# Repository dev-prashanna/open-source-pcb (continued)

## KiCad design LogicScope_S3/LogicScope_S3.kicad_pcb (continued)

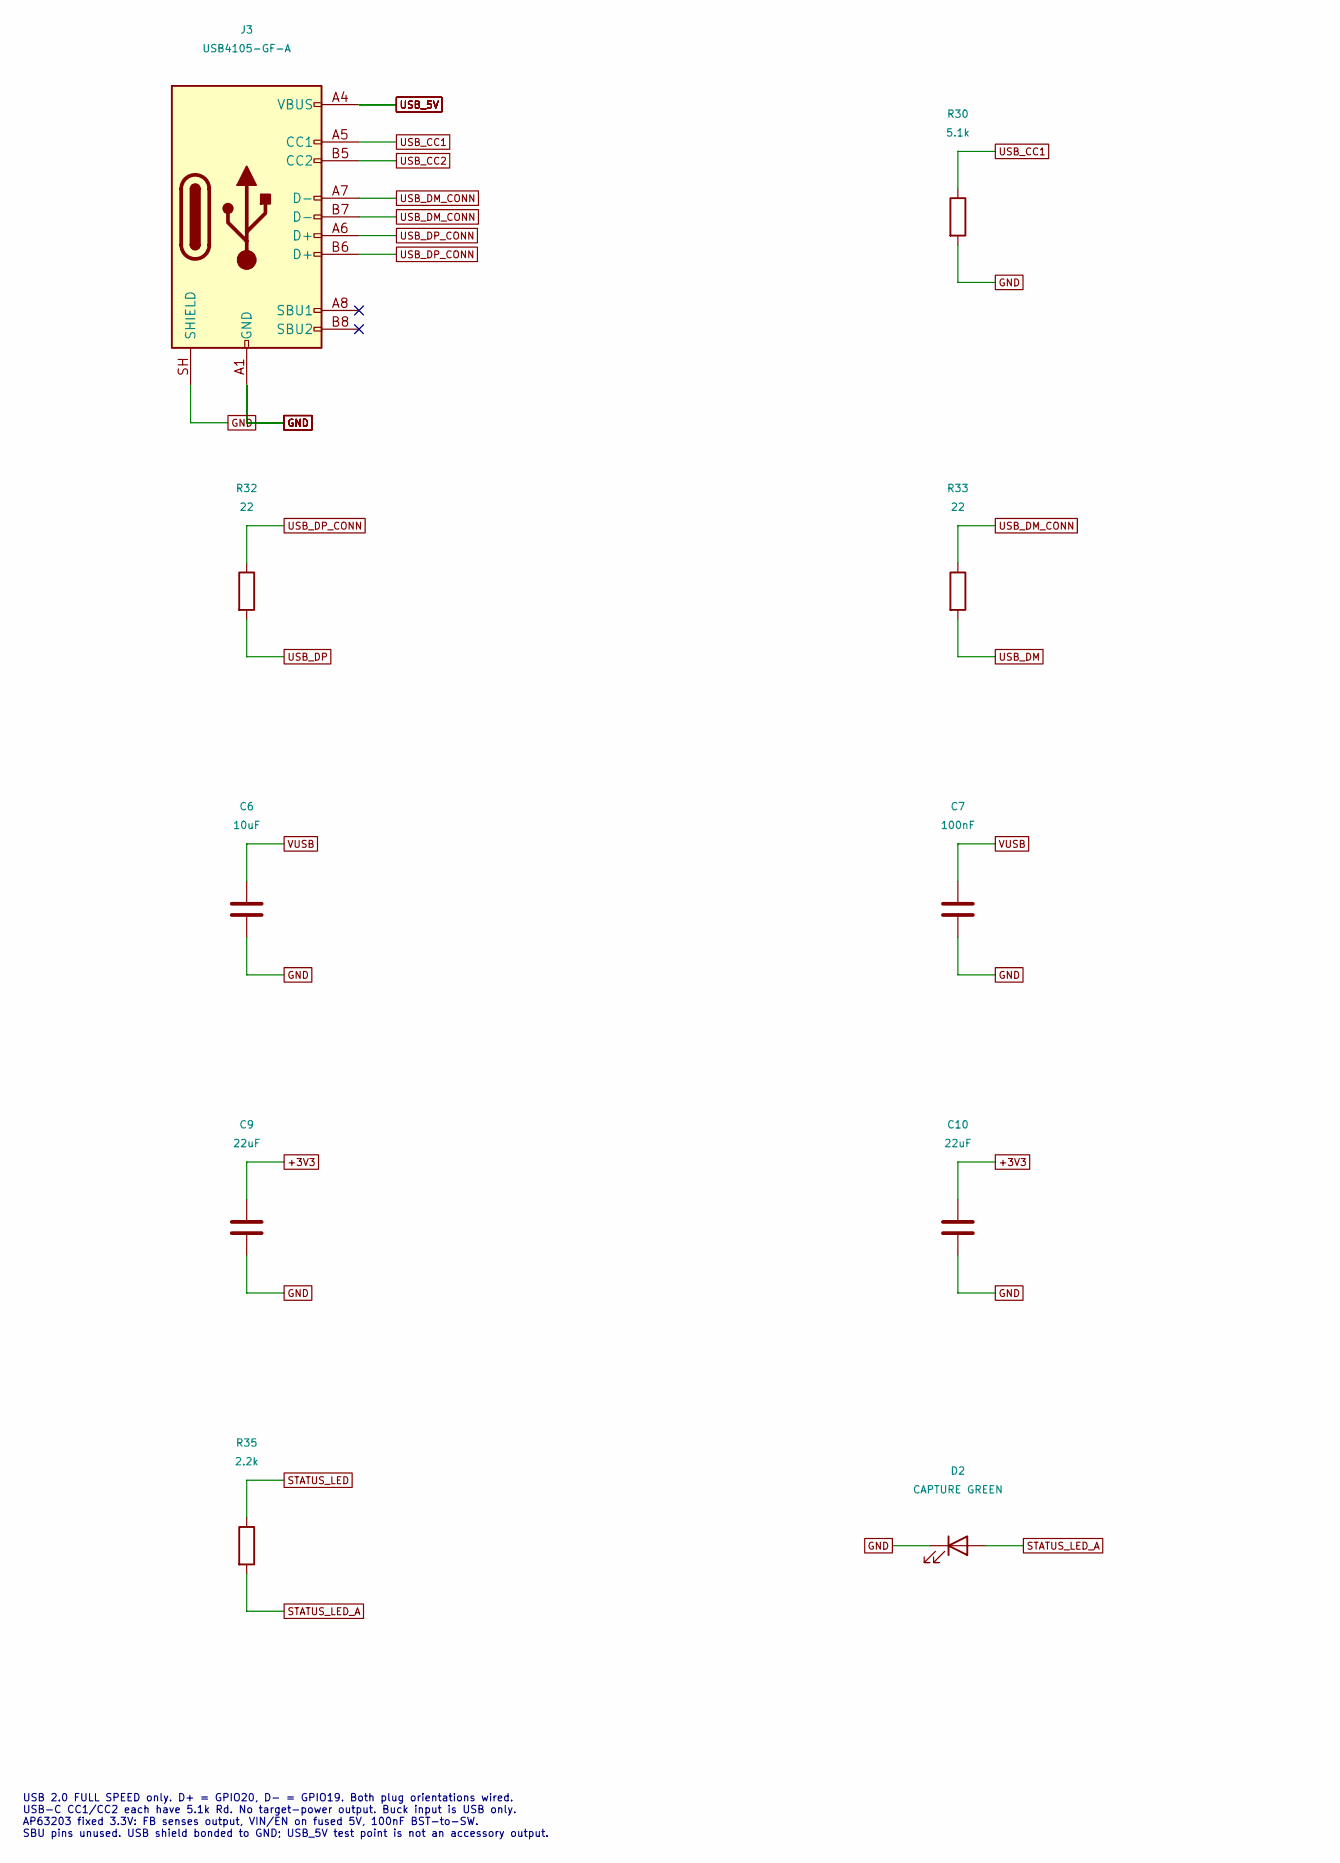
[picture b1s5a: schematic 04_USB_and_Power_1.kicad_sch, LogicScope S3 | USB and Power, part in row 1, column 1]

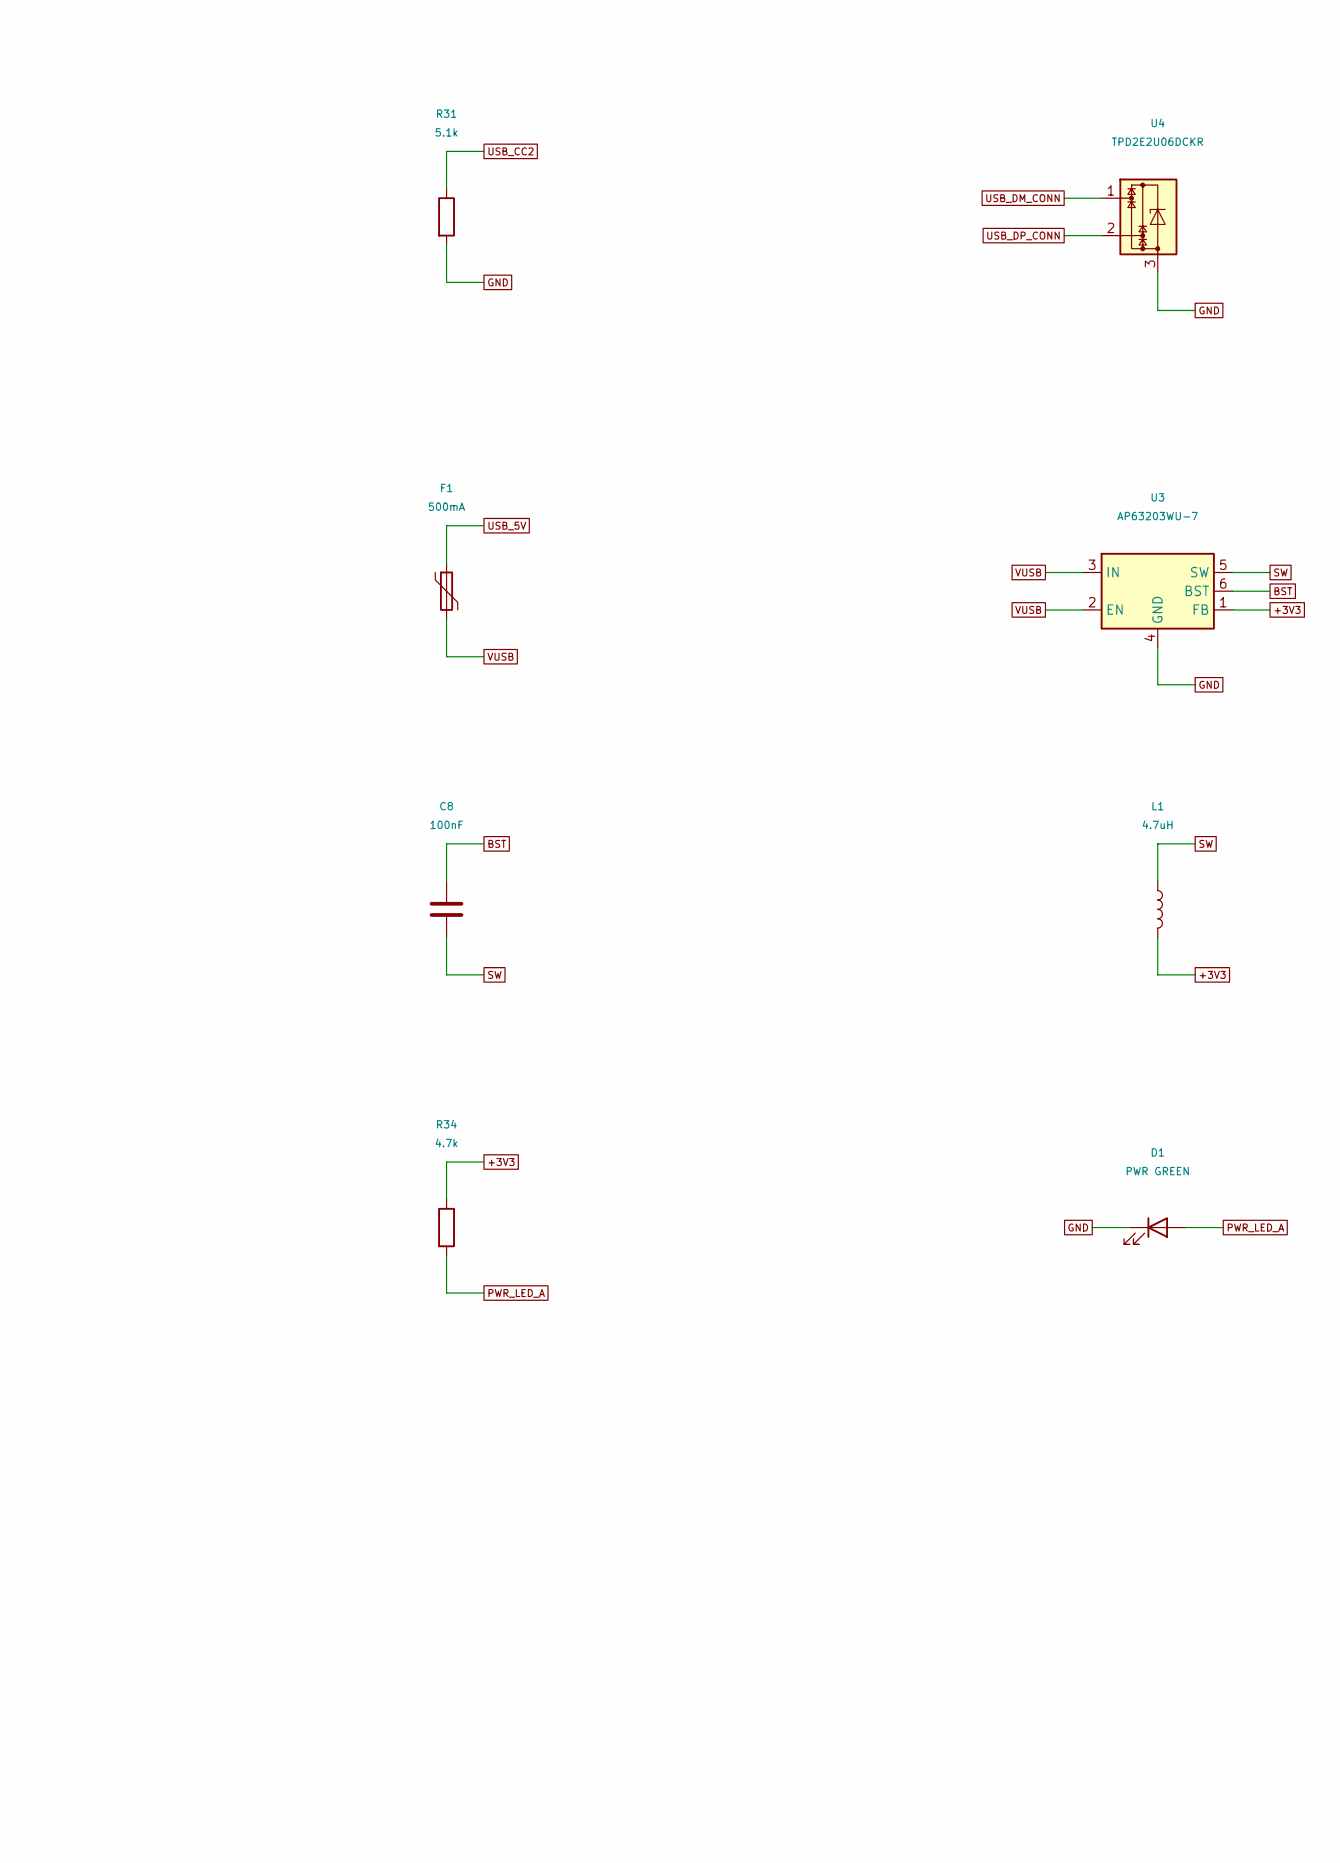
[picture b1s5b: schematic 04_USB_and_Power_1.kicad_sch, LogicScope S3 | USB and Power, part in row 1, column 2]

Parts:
C6: 10uF; C_0805_2012Metric; MPN GRM21BR61A106KE19L
C7, C8: 100nF; C_0603_1608Metric; MPN GRM188R71C104KA01D
C9, C10: 22uF; C_0805_2012Metric; MPN GRM21BR60J226ME39L
D1: PWR GREEN; LED_0603_1608Metric; MPN LTST-C190KGKT
D2: CAPTURE GREEN; LED_0603_1608Metric; MPN LTST-C190KGKT
F1: 500mA; Fuse_1206_3216Metric; MPN 1206L050YR
J3: USB4105-GF-A; USB_C_Receptacle_GCT_USB4105-xx-A_16P_TopMnt_Horizontal; MPN USB4105-GF-A
L1: 4.7uH; L_Bourns-SRN4018; MPN SRN4018-4R7M
R30, R31: 5.1k; R_0603_1608Metric; MPN RC0603FR-075K1L
R32, R33: 22; R_0402_1005Metric; MPN RC0402FR-0722RL
R34: 4.7k; R_0603_1608Metric; MPN RC0603FR-074K7L
R35: 2.2k; R_0603_1608Metric; MPN RC0603FR-072K2L
U3: AP63203WU-7; TSOT-23-6; MPN AP63203WU-7
U4: TPD2E2U06DCKR; SOT-323_SC-70; MPN TPD2E2U06DCKR

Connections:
+3V3: C9.1, C10.1, L1.2, R34.1, U3.1 (FB); also elsewhere on the board
BST: C8.1, U3.6 (BST)
GND: C6.2, C7.2, C9.2, C10.2, D1.1 (K), D2.1 (K), J3.A1 (GND), J3.A12 (GND), J3.B1 (GND), J3.B12 (GND), J3.SH (SHIELD), R30.2, R31.2, U3.4 (GND), U4.3; also elsewhere on the board
PWR_LED_A: D1.2 (A), R34.2
STATUS_LED: R35.1; also elsewhere on the board
STATUS_LED_A: D2.2 (A), R35.2
SW: C8.2, L1.1, U3.5 (SW)
USB_5V: F1.1, J3.A4 (VBUS), J3.A9 (VBUS), J3.B4 (VBUS), J3.B9 (VBUS); also elsewhere on the board
USB_CC1: J3.A5 (CC1), R30.1
USB_CC2: J3.B5 (CC2), R31.1
USB_DM: R33.2; also elsewhere on the board
USB_DM_CONN: J3.A7 (D-), J3.B7 (D-), R33.1, U4.1
USB_DP: R32.2; also elsewhere on the board
USB_DP_CONN: J3.A6 (D+), J3.B6 (D+), R32.1, U4.2
VUSB: C6.1, C7.1, F1.2, U3.2 (EN), U3.3 (IN); also elsewhere on the board

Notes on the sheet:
USB 2.0 FULL SPEED only. D+ = GPIO20, D- = GPIO19. Both plug orientations wired. USB-C CC1/CC2 each have 5.1k Rd. No target-power output. Buck input is USB only. AP63203 fixed 3.3V: FB senses output, VIN/EN on fused 5V, 100nF BST-to-SW. SBU pins unused. USB shield bonded to GND; USB_5V test point i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

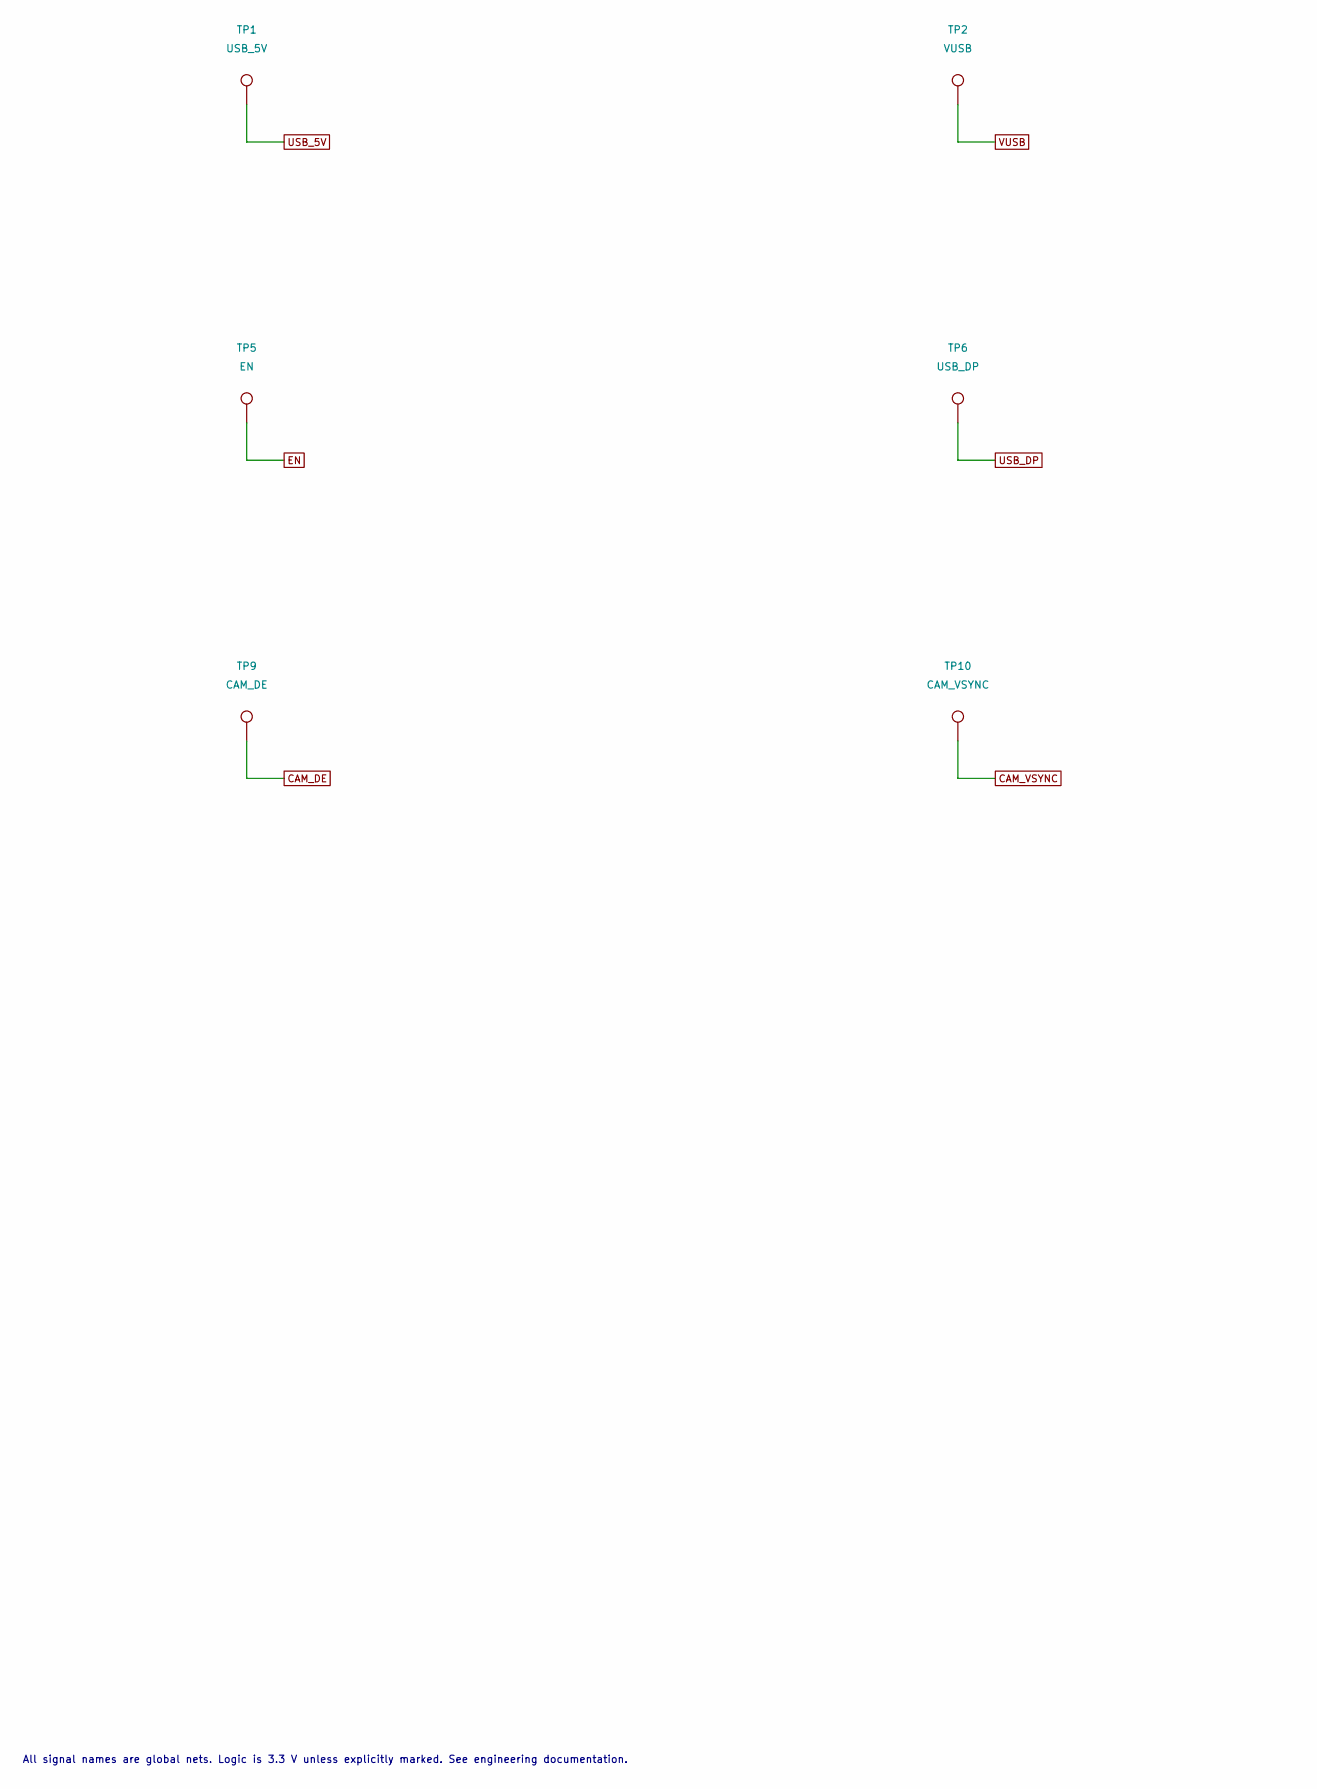
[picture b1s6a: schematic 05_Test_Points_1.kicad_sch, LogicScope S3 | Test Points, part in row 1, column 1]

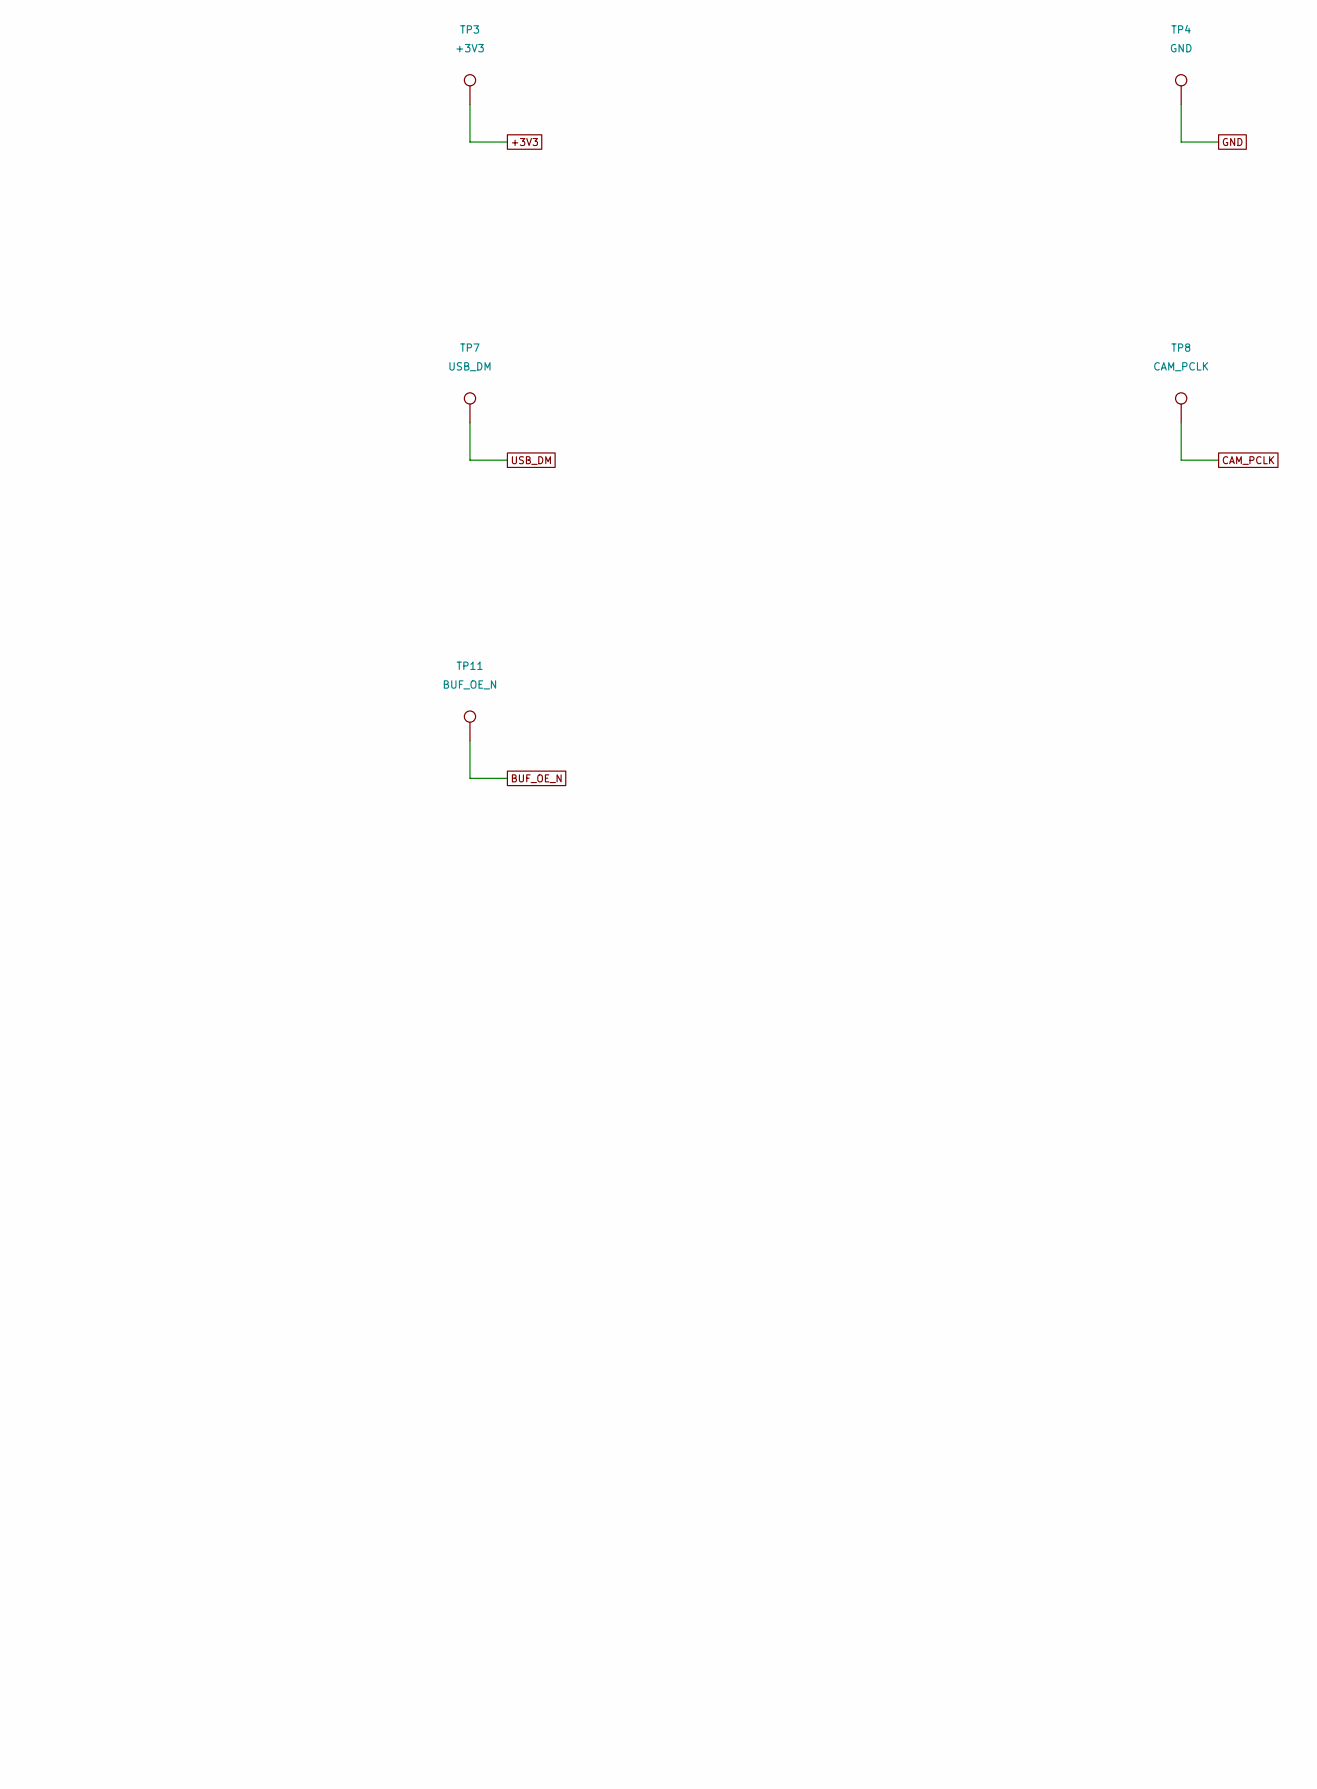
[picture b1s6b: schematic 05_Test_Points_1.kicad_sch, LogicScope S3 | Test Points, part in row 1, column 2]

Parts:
TP1: USB_5V; TestPoint_Pad_D1.0mm; MPN PCB_PAD
TP2: VUSB; TestPoint_Pad_D1.0mm; MPN PCB_PAD
TP3: +3V3; TestPoint_Pad_D1.0mm; MPN PCB_PAD
TP4: GND; TestPoint_Pad_D1.0mm; MPN PCB_PAD
TP5: EN; TestPoint_Pad_D1.0mm; MPN PCB_PAD
TP6: USB_DP; TestPoint_D0.5mm; MPN PCB_PAD
TP7: USB_DM; TestPoint_D0.5mm; MPN PCB_PAD
TP8: CAM_PCLK; TestPoint_Pad_D1.0mm; MPN PCB_PAD
TP9: CAM_DE; TestPoint_Pad_D1.0mm; MPN PCB_PAD
TP10: CAM_VSYNC; TestPoint_Pad_D1.0mm; MPN PCB_PAD
TP11: BUF_OE_N; TestPoint_Pad_D1.0mm; MPN PCB_PAD

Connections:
+3V3: TP3.1; also elsewhere on the board
BUF_OE_N: TP11.1; also elsewhere on the board
CAM_DE: TP9.1; also elsewhere on the board
CAM_PCLK: TP8.1; also elsewhere on the board
CAM_VSYNC: TP10.1; also elsewhere on the board
EN: TP5.1; also elsewhere on the board
GND: TP4.1; also elsewhere on the board
USB_5V: TP1.1; also elsewhere on the board
USB_DM: TP7.1; also elsewhere on the board
USB_DP: TP6.1; also elsewhere on the board
VUSB: TP2.1; also elsewhere on the board

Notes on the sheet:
All signal names are global nets. Logic is 3.3 V unless explicitly marked. See engineering documentation.

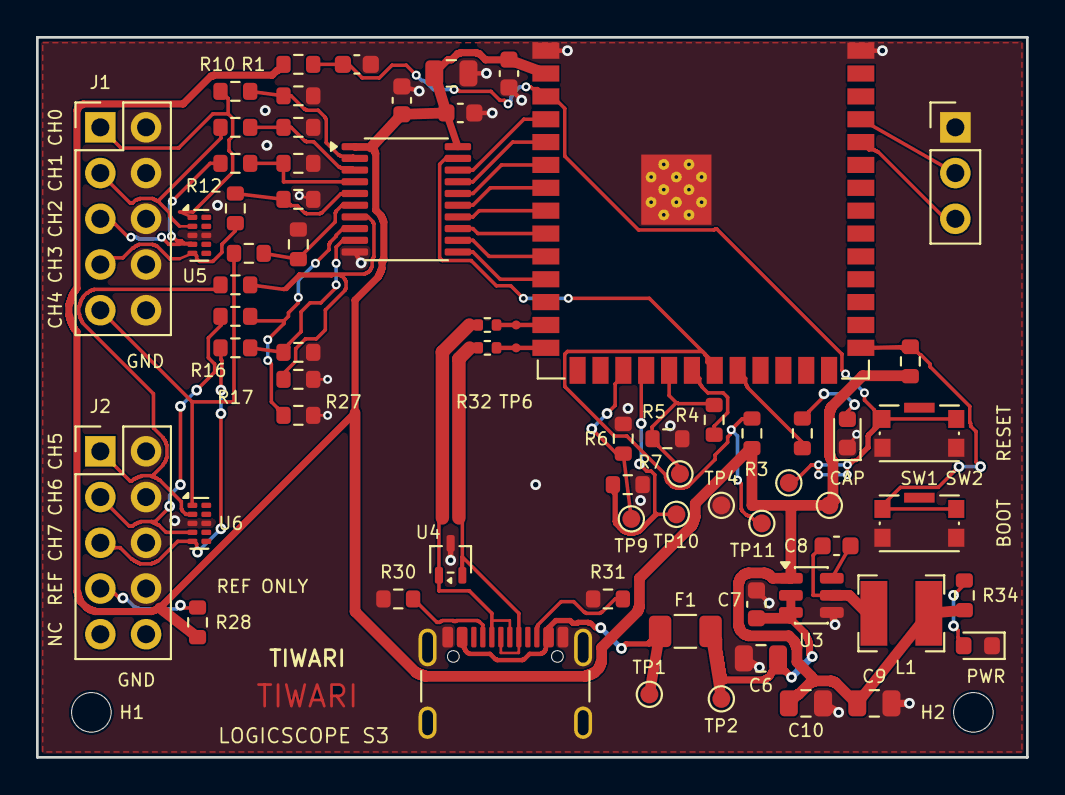
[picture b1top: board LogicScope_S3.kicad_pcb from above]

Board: 2 copper layers, 55.0 x 40.0 mm, 69 parts (0 on the bottom side), 49 nets.

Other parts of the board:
H1, H2: MountingHole_2.2mm_M2

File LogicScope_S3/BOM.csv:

Reference,Value,MPN,Manufacturer,Footprint,DNP,Datasheet
U1,ESP32-S3-WROOM-1-N8R2,ESP32-S3-WROOM-1-N8R2,Espressif,LogicScope:ESP32-S3-WROOM-1_Overhang,NO,https://documentation.espressif.com/esp32-s3-wroom-1_wroom-1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
C1,100nF,GRM188R71C104KA01D,Murata,Capacitor_SMD:C_0603_1608Metric,NO,https://www.murata.com/en-global/products/capacitor/ceramicc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
C2,10uF,GRM21BR61A106KE19L,Murata,Capacitor_SMD:C_0805_2012Metric,NO,https://www.murata.com/en-global/products/capacitor/ceramicc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
R1,10k,RC0603FR-0710KL,Yageo,Resistor_SMD:R_0603_1608Metric,NO,https://www.yageo.com/en/Product/Index/rchip
C3,1uF,GRM188R61A105KA61D,Murata,Capacitor_SMD:C_0603_1608Metric,NO,https://www.murata.com/en-global/products/capacitor/ceramicc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
R2,10k,RC0603FR-0710KL,Yageo,Resistor_SMD:R_0603_1608Metric,NO,https://www.yageo.com/en/Product/Index/rchip
R3,10k,RC0603FR-0710KL,Yageo,Resistor_SMD:R_0603_1608Metric,NO,https://www.yageo.com/en/Product/Index/rchip
R4,33,RC0603FR-0733RL,Yageo,Resistor_SMD:R_0603_1608Metric,NO,https://www.yageo.com/en/Product/Index/rchip
R5,100k,RC0603FR-07100KL,Yageo,Resistor_SMD:R_0603_1608Metric,NO,https://www.yageo.com/en/Product/Index/rchip
R6,100k,RC0603FR-07100KL,Yageo,Resistor_SMD:R_0603_1608Metric,NO,https://www.yageo.com/en/Product/Index/rchip
R7,100k,RC0603FR-07100KL,Yageo,Resistor_SMD:R_0603_1608Metric,NO,https://www.yageo.com/en/Product/Index/rchip
SW1,RESET,KMR221GLFS,C&K,Button_Switch_SMD:SW_Push_1P1T-SH_NO_CK_KMR2xxG,NO,https://www.ckswitches.com/media/1464/kmr2.pdf
SW2,BOOT,KMR221GLFS,C&K,Button_Switch_SMD:SW_Push_1P1T-SH_NO_CK_KMR2xxG,NO,https://www.ckswitches.com/media/1464/kmr2.pdf
J4,DEBUG 3V3 UART,61300311121,Wurth Elektronik,Connector_PinHeader_2.54mm:PinHeader_1x03_P2.54mm_Vertical,NO,https://www.we-online.com/en/components/products/WR-PHD_254M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
J1,CH0..4 + GROUNDS,61301021121,Wurth Elektronik,Connector_PinHeader_2.54mm:PinHeader_2x05_P2.54mm_Vertical,NO,https://www.we-online.com/en/components/products/WR-PHD_254M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
J2,CH5..7 / REF ONLY,61301021121,Wurth Elektronik,Connector_PinHeader_2.54mm:PinHeader_2x05_P2.54mm_Vertical,NO,https://www.we-online.com/en/components/products/WR-PHD_254M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
R10,220,RC0603FR-07220RL,Yageo,Resistor_SMD:R_0603_1608Metric,NO,https://www.yageo.com/en/Product/Index/rchip
R20,100k,RC0603FR-07100KL,Yageo,Resistor_SMD:R_0603_1608Metric,NO,https://www.yageo.com/en/Product/Index/rchip
R11,220,RC0603FR-07220RL,Yageo,Resistor_SMD:R_0603_1608Metric,NO,https://www.yageo.com/en/Product/Index/rchip
R21,100k,RC0603FR-07100KL,Yageo,Resistor_SMD:R_0603_1608Metric,NO,https://www.yageo.com/en/Product/Index/rchip
R12,220,RC0603FR-07220RL,Yageo,Resistor_SMD:R_0603_1608Metric,NO,https://www.yageo.com/en/Product/Index/rchip
R22,100k,RC0603FR-07100KL,Yageo,Resistor_SMD:R_0603_1608Metric,NO,https://www.yageo.com/en/Product/Index/rchip
R13,220,RC0603FR-07220RL,Yageo,Resistor_SMD:R_0603_1608Metric,NO,https://www.yageo.com/en/Product/Index/rchip
R23,100k,RC0603FR-07100KL,Yageo,Resistor_SMD:R_0603_1608Metric,NO,https://www.yageo.com/en/Product/Index/rchip
R14,220,RC0603FR-07220RL,Yageo,Resistor_SMD:R_0603_1608Metric,NO,https://www.yageo.com/en/Product/Index/rchip
R24,100k,RC0603FR-07100KL,Yageo,Resistor_SMD:R_0603_1608Metric,NO,https://www.yageo.com/en/Product/Index/rchip
R15,220,RC0603FR-07220RL,Yageo,Resistor_SMD:R_0603_1608Metric,NO,https://www.yageo.com/en/Product/Index/rchip
R25,100k,RC0603FR-07100KL,Yageo,Resistor_SMD:R_0603_1608Metric,NO,https://www.yageo.com/en/Product/Index/rchip
R16,220,RC0603FR-07220RL,Yageo,Resistor_SMD:R_0603_1608Metric,NO,https://www.yageo.com/en/Product/Index/rchip
R26,100k,RC0603FR-07100KL,Yageo,Resistor_SMD:R_0603_1608Metric,NO,https://www.yageo.com/en/Product/Index/rchip
R17,220,RC0603FR-07220RL,Yageo,Resistor_SMD:R_0603_1608Metric,NO,https://www.yageo.com/en/Product/Index/rchip
R27,100k,RC0603FR-07100KL,Yageo,Resistor_SMD:R_0603_1608Metric,NO,https://www.yageo.com/en/Product/Index/rchip
R28,10k,RC0603FR-0710KL,Yageo,Resistor_SMD:R_0603_1608Metric,NO,https://www.yageo.com/en/Product/Index/rchip
U5,TPD4E05U06DQAR (OPTIONAL),TPD4E05U06DQAR,Texas Instruments,Package_SON:USON-10_2.5x1.0mm_P0.5mm,YES,https://www.ti.com/lit/ds/symlink/tpd4e05u06.pdf
U6,TPD4E05U06DQAR (OPTIONAL),TPD4E05U06DQAR,Texas Instruments,Package_SON:USON-10_2.5x1.0mm_P0.5mm,YES,https://www.ti.com/lit/ds/symlink/tpd4e05u06.pdf
U2,SN74LVC245APW,SN74LVC245APW,Texas Instruments,Package_SO:TSSOP-20_4.4x6.5mm_P0.65mm,NO,https://www.ti.com/lit/ds/symlink/sn74lvc245a.pdf
C4,100nF,GRM188R71C104KA01D,Murata,Capacitor_SMD:C_0603_1608Metric,NO,https://www.murata.com/en-global/products/capacitor/ceramicc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
C5,1uF,GRM188R61A105KA61D,Murata,Capacitor_SMD:C_0603_1608Metric,NO,https://www.murata.com/en-global/products/capacitor/ceramicc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
J3,USB4105-GF-A,USB4105-GF-A,GCT,Connector_USB:USB_C_Receptacle_GCT_USB4105-xx-A_16P_TopMnt_Horizontal,NO,https://gct.co/connector/usb4105
R30,5.1k,RC0603FR-075K1L,Yageo,Resistor_SMD:R_0603_1608Metric,NO,https://www.yageo.com/en/Product/Index/rchip
R31,5.1k,RC0603FR-075K1L,Yageo,Resistor_SMD:R_0603_1608Metric,NO,https://www.yageo.com/en/Product/Index/rchip
U4,TPD2E2U06DCKR,TPD2E2U06DCKR,Texas Instruments,Package_TO_SOT_SMD:SOT-323_SC-70,NO,https://www.ti.com/lit/ds/symlink/tpd2e2u06.pdf
R32,22,RC0402FR-0722RL,Yageo,Resistor_SMD:R_0402_1005Metric,NO,https://www.yageo.com/en/Product/Index/rchip
R33,22,RC0402FR-0722RL,Yageo,Resistor_SMD:R_0402_1005Metric,NO,https://www.yageo.com/en/Product/Index/rchip
F1,500mA,1206L050YR,Littelfuse,Fuse:Fuse_1206_3216Metric,NO,https://www.littelfuse.com/products/polyswitch-resettable-pp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
U3,AP63203WU-7,AP63203WU-7,Diodes Incorporated,Package_TO_SOT_SMD:TSOT-23-6,NO,https://www.diodes.com/assets/Datasheets/AP63200-AP63201-AP6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
C6,10uF,GRM21BR61A106KE19L,Murata,Capacitor_SMD:C_0805_2012Metric,NO,https://www.murata.com/en-global/products/capacitor/ceramicc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
C7,100nF,GRM188R71C104KA01D,Murata,Capacitor_SMD:C_0603_1608Metric,NO,https://www.murata.com/en-global/products/capacitor/ceramicc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
C8,100nF,GRM188R71C104KA01D,Murata,Capacitor_SMD:C_0603_1608Metric,NO,https://www.murata.com/en-global/products/capacitor/ceramicc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
L1,4.7uH,SRN4018-4R7M,Bourns,Inductor_SMD:L_Bourns-SRN4018,NO,https://www.bourns.com/docs/product-datasheets/srn4018.pdf
C9,22uF,GRM21BR60J226ME39L,Murata,Capacitor_SMD:C_0805_2012Metric,NO,https://www.murata.com/en-global/products/capacitor/ceramicc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
C10,22uF,GRM21BR60J226ME39L,Murata,Capacitor_SMD:C_0805_2012Metric,NO,https://www.murata.com/en-global/products/capacitor/ceramicc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
R34,4.7k,RC0603FR-074K7L,Yageo,Resistor_SMD:R_0603_1608Metric,NO,https://www.yageo.com/en/Product/Index/rchip
D1,PWR GREEN,LTST-C190KGKT,Lite-On,LED_SMD:LED_0603_1608Metric,NO,
R35,2.2k,RC0603FR-072K2L,Yageo,Resistor_SMD:R_0603_1608Metric,NO,https://www.yageo.com/en/Product/Index/rchip
D2,CAPTURE GREEN,LTST-C190KGKT,Lite-On,LED_SMD:LED_0603_1608Metric,NO,

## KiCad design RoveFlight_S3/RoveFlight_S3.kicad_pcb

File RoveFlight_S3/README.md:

# RoveFlight S3

**RF-S3-A0 — compact ESP32-S3 flight-controller engineering prototype for a 1S brushed quadcopter.**

Hardware layout release completed 2026-11-09: **ERC 0, DRC 0, unconnected items 0, schematic/PCB parity issues 0**, with all 15 independent connectivity checks passing. [Manufacturing package](fabrication/) and [validation evidence](docs/Manufacturing_Readiness.md) are included. Via-in-pad filling/capping and fabricator DFM are required; physical qualification remains open.

A real native KiCad design with ESP32-S3-WROOM-1-N8R2, four independent brushed-motor MOSFET stages, a hardware arming latch and watchdog, BMI270 SPI IMU, BMP390 SPI barometer, battery voltage/current monitoring, downward VL53L1X, IR receiver, USB-C and receiver/optical-flow/debug expansion.

Open **RoveFlight_S3.kicad_pro** in KiCad 10. The root schematic links the functional sheets. The PCB is 45 x 45 mm, six layers, nominal 1.0-mm thickness, two-sided assembly, with 25.5-mm-square M2 mounting and an antenna overhang. The assembled antenna extends 6.75 mm beyond the forward edge. No flight-ready, fabricated-board, RF, thermal or EMC qualification is claimed.

## Electrical limits

- Protected 1S LiPo, 3.1–4.2 V. No onboard charger or cell-protection IC.
- Brushed motors only. Proposed envelope: 1 A continuous per motor, 4 A aggregate, 2 A single-channel stall for at most 100 ms, subject to actual motor/propeller and thermal qualification.
- All external signals are 3.3 V. Receiver supply/interface compatibility must be checked; no 5-V UART tolerance or SBUS inverter is provided.
- Remove JP1 to disconnect motor enable physically. USB insertion clears the arming latch. Every detected fault requires a fresh arming command; see the exact reset caveat in the safety document.
- Local attitude stabilization, failsafes, calibration, PID, mixing, telemetry, configuration, OTA and logging require firmware. The supplied bring-up skeleton only holds motors disabled and blinks the status LED.

## Engineering documentation

- [Motor numbering, calculations and interlock](docs/Motors_and_Safety.md)
- [Battery and power architecture](docs/Power_Architecture.md)
- [GPIO allocation](docs/GPIO_Allocation.md)
- [Sensor orientation and mechanics](docs/Sensors_and_Mechanics.md)
- [Recommended firmware architecture](docs/Firmware_Architecture.md)
- [Bring-up and qualification procedure](docs/Bringup_and_Validation.md)
- [Manufacturing readiness](docs/Manufacturing_Readiness.md)

BOM.csv and BOM_Grouped.csv include part numbers and footprint assignments. GPIO_Allocation.csv, Connector_Pinouts.csv and Placement.csv provide machine-readable implementation references. Manufacturer sources are recorded in datasheets/sources.json. Manufacturer catalogue listing was checked for the N8R2 variant; no distributor stock reservation or guaranteed BOM availability is claimed.

The N8R2 variant provides 8-MB Quad SPI flash and 2-MB Quad PSRAM in an 18 x 25.5 x 3.1-mm module. N8 without PSRAM was considered but leaves less buffering for logs/telemetry; N8R8 adds memory and a different memory configuration without a need in this initial design. Neither is an automatic assembly substitution. The antenna carrier-board keepout follows the official module footprint and Espressif hardware guidelines; frame, battery and wiring clearance still need RF validation.

## Construction and verification

To check and export the current design without rebuilding its placement or routing, run `python scripts/release.py` in the configured Python environment. It gates manufacturing exports on ERC, DRC, parity and connectivity checks. Verify the resulting package from this directory with `sha256sum -c fabrication/SHA256SUMS`.

Scripts require KiCad 10 system Python bindings and requirements.txt. The project was initialized and the controller instantiated through the connected KiCad MCP server; native Python construction expands the complete hierarchical schematic and board using installed KiCad libraries and an explicit pin-to-net manifest. MCP/CLI ERC and DRC provide independent validation.

The construction sequence is build_design.py -> KiCad XML netlist export -> layout.py -> prepare_routing.py -> assisted Specctra routing -> import_routing.py -> any documented repairs -> silkscreen.py -> audit_design.py and final ERC/DRC/export. **build_design.py rebuilds the schematic; layout.py clears routing. Work on a copy when experimenting.** These are engineering construction scripts, not a flight-qualified unattended release pipeline.

Original project assets are licensed under CERN-OHL-P-2.0; see LICENSE. KiCad library-derived content retains its upstream licence and exception, recorded in libraries/README.md and libraries/KiCad-LICENSE.md.

[Bottom assembly preview](previews/PCB_bottom.png). Renders show assigned library models; missing connector/sensor models are represented by their board land patterns.

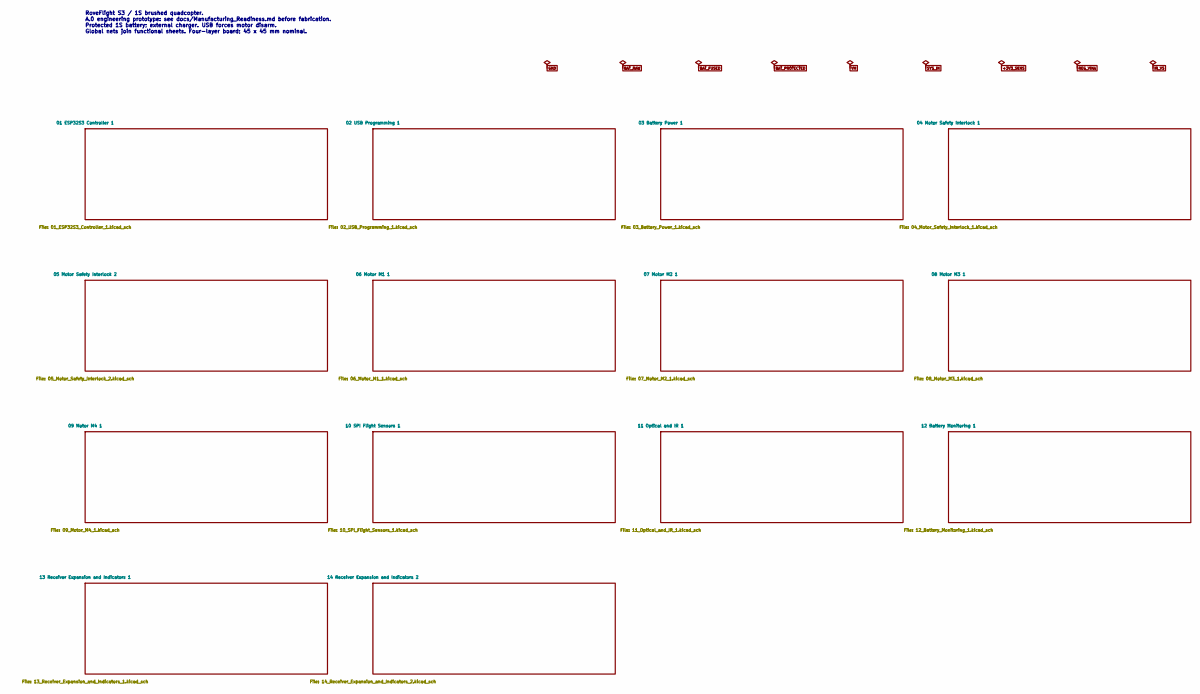
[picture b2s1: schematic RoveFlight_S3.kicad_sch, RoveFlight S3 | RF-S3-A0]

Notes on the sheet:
RoveFlight S3 / 1S brushed quadcopter. A.0 engineering prototype: see docs/Manufacturing_Readiness.md before fabrication. Protected 1S battery; external charger. USB forces motor disarm. Global nets join functional sheets. Four-layer board; 45 x 45 mm nominal.
